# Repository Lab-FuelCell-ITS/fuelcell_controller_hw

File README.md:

# Fuel Cell Controller — Hardware

This repository contains the KiCad schematic and PCB hardware design for the Fuel Cell Controller developed by **Lab-FuelCell-ITS**. The project includes complete KiCad source files, symbol/footprint libraries, and backups used for designing, modifying, and fabricating the controller board.

<!-- 
 -->
<div style="display: flex; justify-content: center; gap: 10px;">

</div>

---

## Features

- Full KiCad project (schematics + PCB layout)
- Custom symbol and footprint libraries
- Backup snapshots for restoration
- Ready for Gerber and BOM generation
- Structured for collaboration and long-term maintenance

---

## Repository Contents

- `fuelcell.kicad_pro` — main KiCad project file  
- `fuelcell.kicad_sch` — schematic  
- `fuelcell.kicad_pcb` — PCB layout  
- `fuel_cell_lib.kicad_sym` — symbol library  
- `fuel_cell_foot.pretty/` — footprint library  
- `fuelcell-backups/` — automatic KiCad backups  
- KiCad metadata: `fp-lib-table`, `sym-lib-table`, `fp-info-cache`, etc.

---

## Notes for next update
- CAN label flipped
- added more space between DC-DC connector
- Nextion should supplied from 5v

--- 

## Requirements

- **KiCad (v9 or newer)**  
  Older versions may open the project but can cause compatibility issues.
  
---

## BOM
[BOM](https://docs.google.com/spreadsheets/d/1h5o9iBbPZtMF7gXZkPm5TLBS_tpg8lyO8AkKIXZHr1Q/edit?gid=0#gid=0)

list belanja
---

## How to Open the Project

1. Clone the repository:
   ```bash
   git clone https://github.com/Lab-FuelCell-ITS/fuelcell_controller_hw.git
   cd fuelcell_controller_hw

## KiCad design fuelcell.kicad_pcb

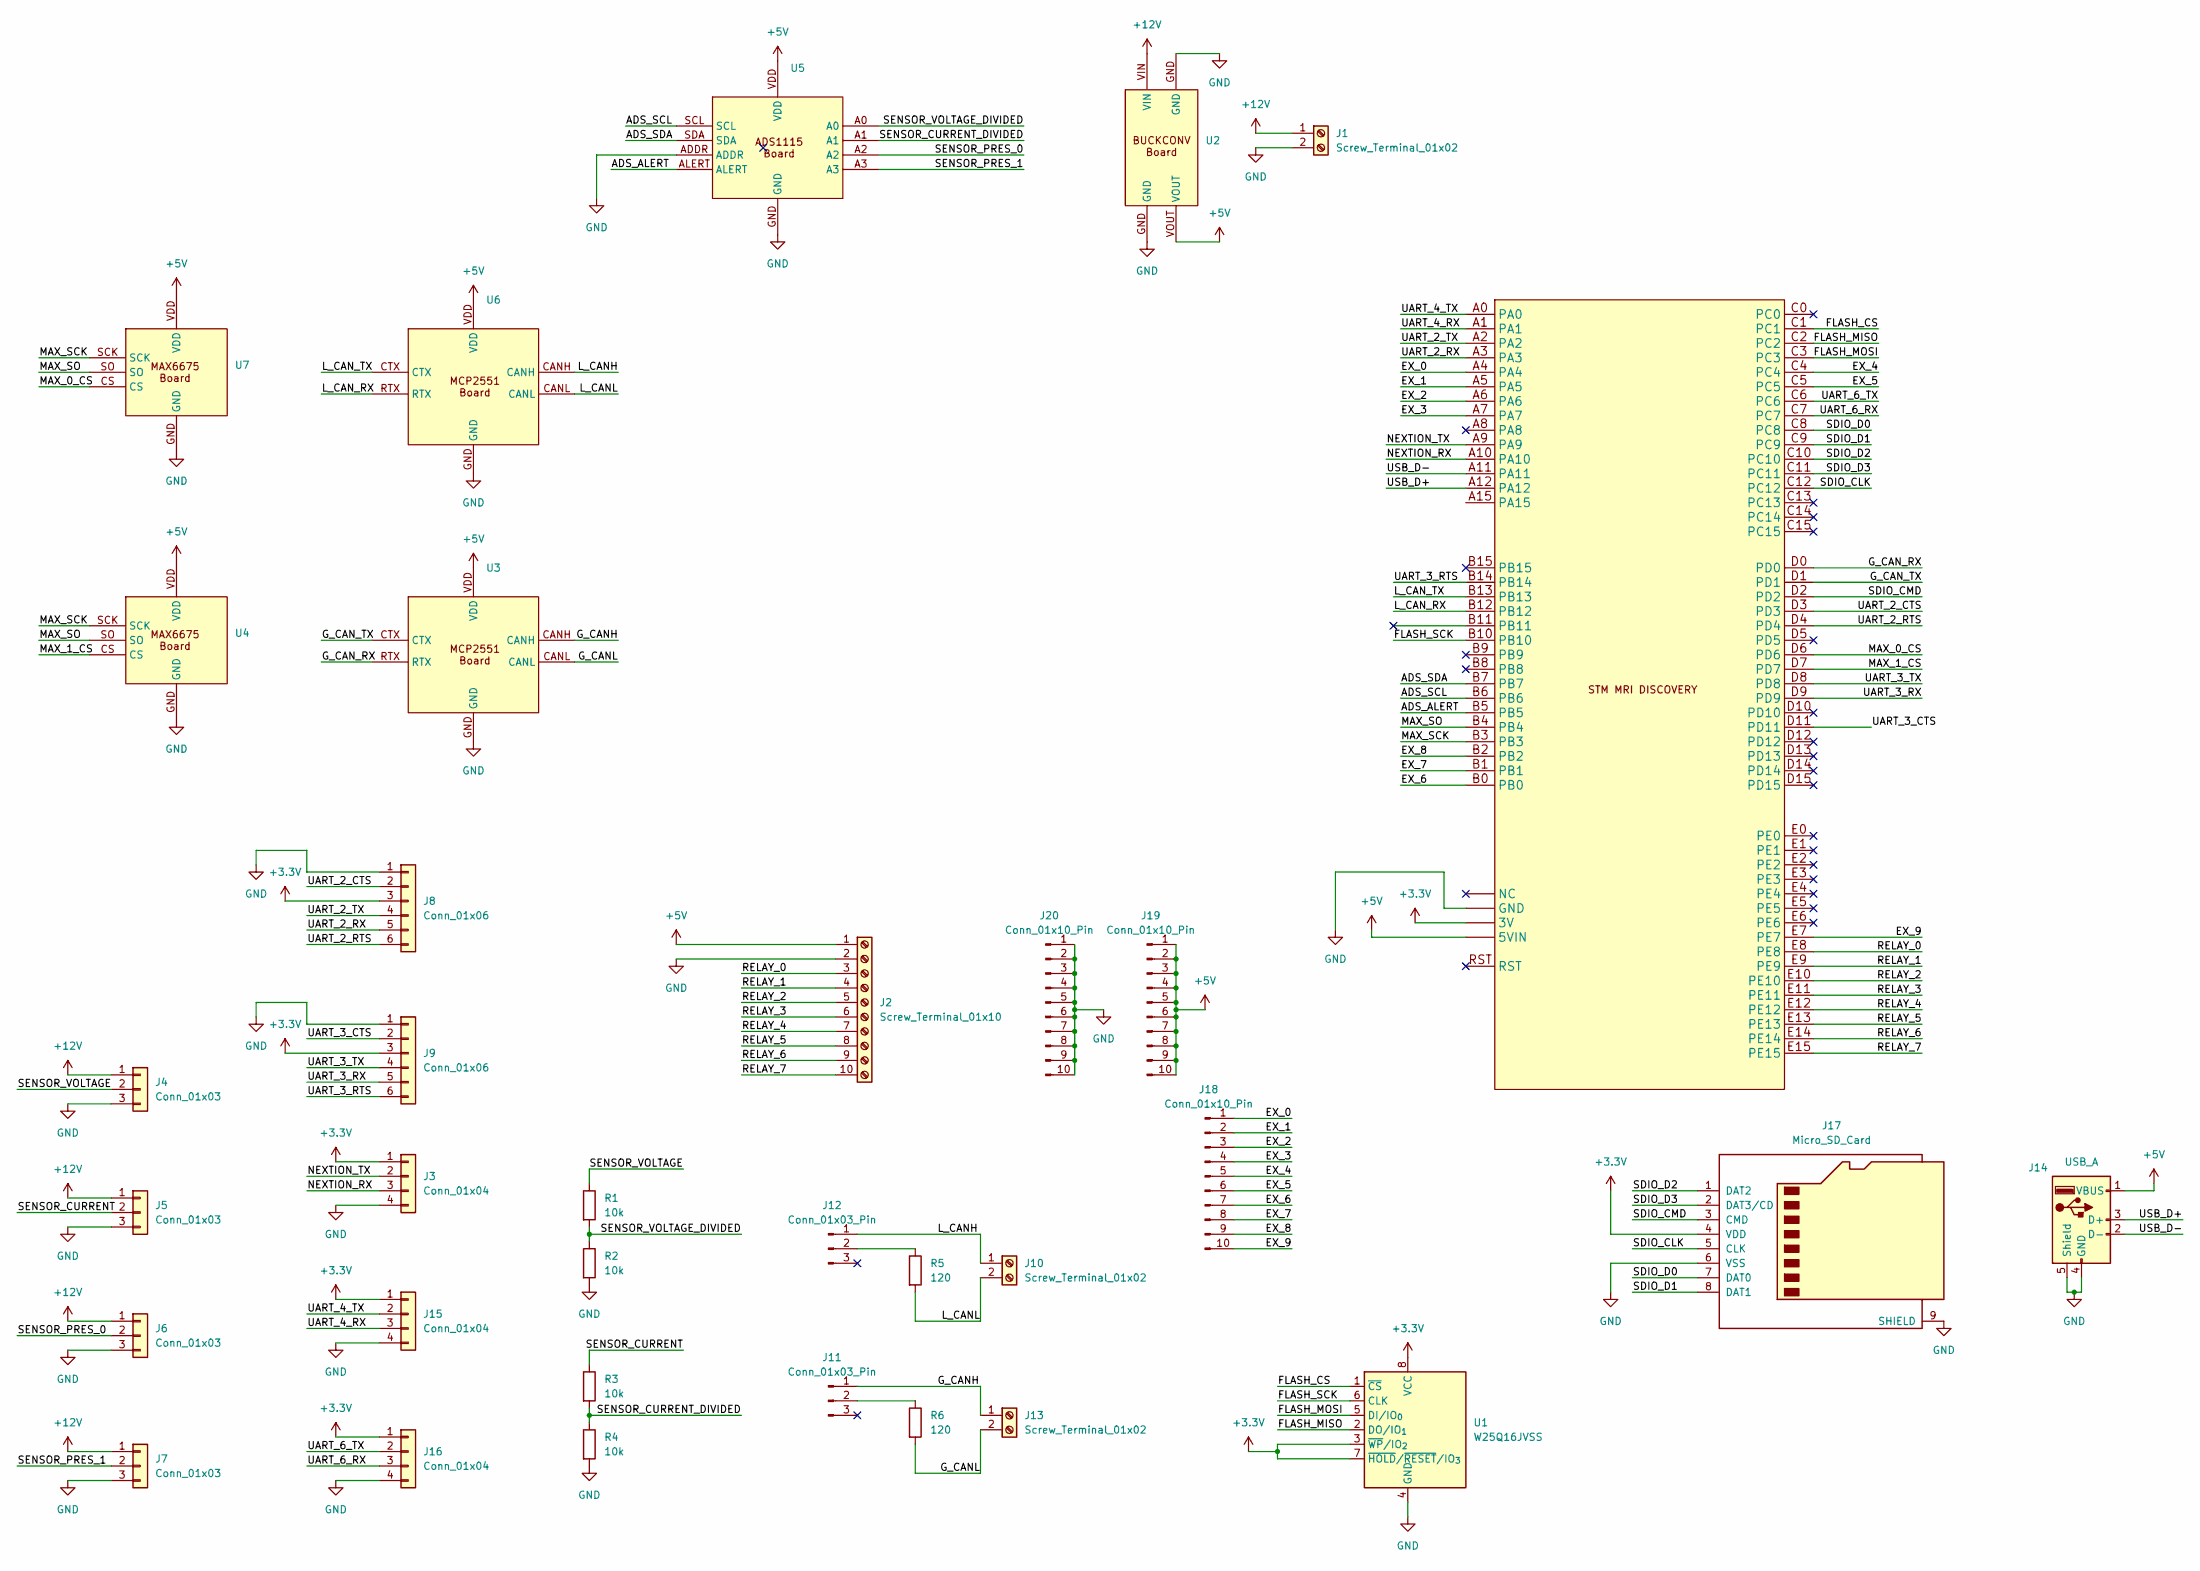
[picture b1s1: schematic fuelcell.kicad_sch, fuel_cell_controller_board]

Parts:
J1, J10, J13: Screw_Terminal_01x02; TerminalBlock_Phoenix_MKDS-1,5-2-5.08_1x02_P5.08mm_Horizont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
J2: Screw_Terminal_01x10; TerminalBlock_Phoenix_MKDS-3-10-5.08_1x10_P5.08mm_Horizontal
J3, J15, J16: Conn_01x04; PinHeader_1x04_P2.54mm_Vertical
J4, J5, J6, J7: Conn_01x03; PinHeader_1x03_P2.54mm_Vertical
J8, J9: Conn_01x06; PinHeader_1x06_P2.54mm_Vertical
J11, J12: Conn_01x03_Pin; PinHeader_1x03_P2.54mm_Vertical
J14: USB_A; USB_A_Molex_67643_Horizontal
J17: Micro_SD_Card; microSD_HC_Molex_47219-2001
J18, J19, J20: Conn_01x10_Pin; PinHeader_1x10_P2.54mm_Vertical
R1, R2, R3, R4: 10k; R_Axial_DIN0207_L6.3mm_D2.5mm_P10.16mm_Horizontal
R5, R6: 120; R_Axial_DIN0207_L6.3mm_D2.5mm_P10.16mm_Horizontal
U1: W25Q16JVSS; SOIC-8_5.3x5.3mm_P1.27mm
U2: Buck_Board
U3, U6: MCP2551_Board
U4, U7: MAX6675_Board
U5: ADS1115_Board
U8: STM32F4HEAD

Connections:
+3.3V: J3.1, J8.3, J9.3, J15.1, J16.1, J17.4 (VDD), U1.3 (~WP/IO_{2}), U1.7 (~HOLD/~RESET/IO_{3}), U1.8 (VCC), U8.3V1 (3V), U8.3V2 (3V), U8.3V3 (3V)
+5V: J2.1, J14.1 (VBUS), J19.1, J19.2, J19.3, J19.4, J19.5, J19.6, J19.7, J19.8, J19.9, J19.10, U2.VOUT, U3.VDD, U4.VDD, U5.VDD, U6.VDD, U7.VDD, U8.5V1 (5VIN), U8.5V2 (5VIN)
+12V: J1.1, J4.1, J5.1, J6.1, J7.1, U2.VIN
/ADS_ALERT: U5.ALERT, U8.B5
/ADS_SCL: U5.SCL, U8.B6
/ADS_SDA: U5.SDA, U8.B7
/EX_0: J18.1, U8.A4
/EX_1: J18.2, U8.A5
/EX_2: J18.3, U8.A6
/EX_3: J18.4, U8.A7
/EX_4: J18.5, U8.C4
/EX_5: J18.6, U8.C5
/EX_6: J18.7, U8.B0
/EX_7: J18.8, U8.B1
/EX_8: J18.9, U8.B2
/EX_9: J18.10, U8.E7
/FLASH_CS: U1.1 (~CS), U8.C1
/FLASH_MISO: U1.2 (DO/IO_{1}), U8.C2
/FLASH_MOSI: U1.5 (DI/IO_{0}), U8.C3
/FLASH_SCK: U1.6 (CLK), U8.B10
/G_CANH: J11.1, J13.1, U3.CANH
/G_CANL: J13.2, R6.2, U3.CANL
/G_CAN_RX: U3.RTX, U8.D0
/G_CAN_TX: U3.CTX, U8.D1
/L_CANH: J10.1, J12.1, U6.CANH
/L_CANL: J10.2, R5.2, U6.CANL
/L_CAN_RX: U6.RTX, U8.B12
/L_CAN_TX: U6.CTX, U8.B13
/MAX_0_CS: U7.CS, U8.D6
/MAX_1_CS: U4.CS, U8.D7
/MAX_SCK: U4.SCK, U7.SCK, U8.B3
/MAX_SO: U4.SO, U7.SO, U8.B4
/NEXTION_RX: J3.3, U8.A10
/NEXTION_TX: J3.2, U8.A9
/RELAY_0: J2.3, U8.E8
/RELAY_1: J2.4, U8.E9
/RELAY_2: J2.5, U8.E10
/RELAY_3: J2.6, U8.E11
/RELAY_4: J2.7, U8.E12
/RELAY_5: J2.8, U8.E13
/RELAY_6: J2.9, U8.E14
/RELAY_7: J2.10, U8.E15
/SDIO_CLK: J17.5 (CLK), U8.C12
/SDIO_CMD: J17.3 (CMD), U8.D2
/SDIO_D0: J17.7 (DAT0), U8.C8
/SDIO_D1: J17.8 (DAT1), U8.C9
/SDIO_D2: J17.1 (DAT2), U8.C10
/SDIO_D3: J17.2 (DAT3/CD), U8.C11
/SENSOR_CURRENT: J5.2, R3.1
/SENSOR_CURRENT_DIVIDED: R3.2, R4.1, U5.A1
/SENSOR_PRES_0: J6.2, U5.A2
/SENSOR_PRES_1: J7.2, U5.A3
/SENSOR_VOLTAGE: J4.2, R1.1
/SENSOR_VOLTAGE_DIVIDED: R1.2, R2.1, U5.A0
/UART_2_CTS: J8.2, U8.D3
/UART_2_RTS: J8.6, U8.D4
/UART_2_RX: J8.5, U8.A3
/UART_2_TX: J8.4, U8.A2
/UART_3_CTS: J9.2, U8.D11
/UART_3_RTS: J9.6, U8.B14
/UART_3_RX: J9.5, U8.D9
/UART_3_TX: J9.4, U8.D8
/UART_4_RX: J15.3, U8.A1
/UART_4_TX: J15.2, U8.A0
/UART_6_RX: J16.3, U8.C7
/UART_6_TX: J16.2, U8.C6
/USB_D+: J14.3 (D+), U8.A12
/USB_D-: J14.2 (D-), U8.A11
GND: J1.2, J2.2, J3.4, J4.3, J5.3, J6.3, J7.3, J8.1, J9.1, J14.4 (GND), J14.5 (Shield), J15.4, J16.4, J17.6 (VSS), J17.9 (SHIELD), J20.1, J20.2, J20.3, J20.4, J20.5, J20.6, J20.7, J20.8, J20.9, J20.10, R2.2, R4.2, U1.4 (GND), U2.GND, U3.GND, U4.GND, U5.ADDR, U5.GND, U6.GND, U7.GND, U8.GND1 (GND), U8.GND2 (GND), U8.GND3 (GND)
unnamed: J11.2, R6.1
unnamed: J12.2, R5.1

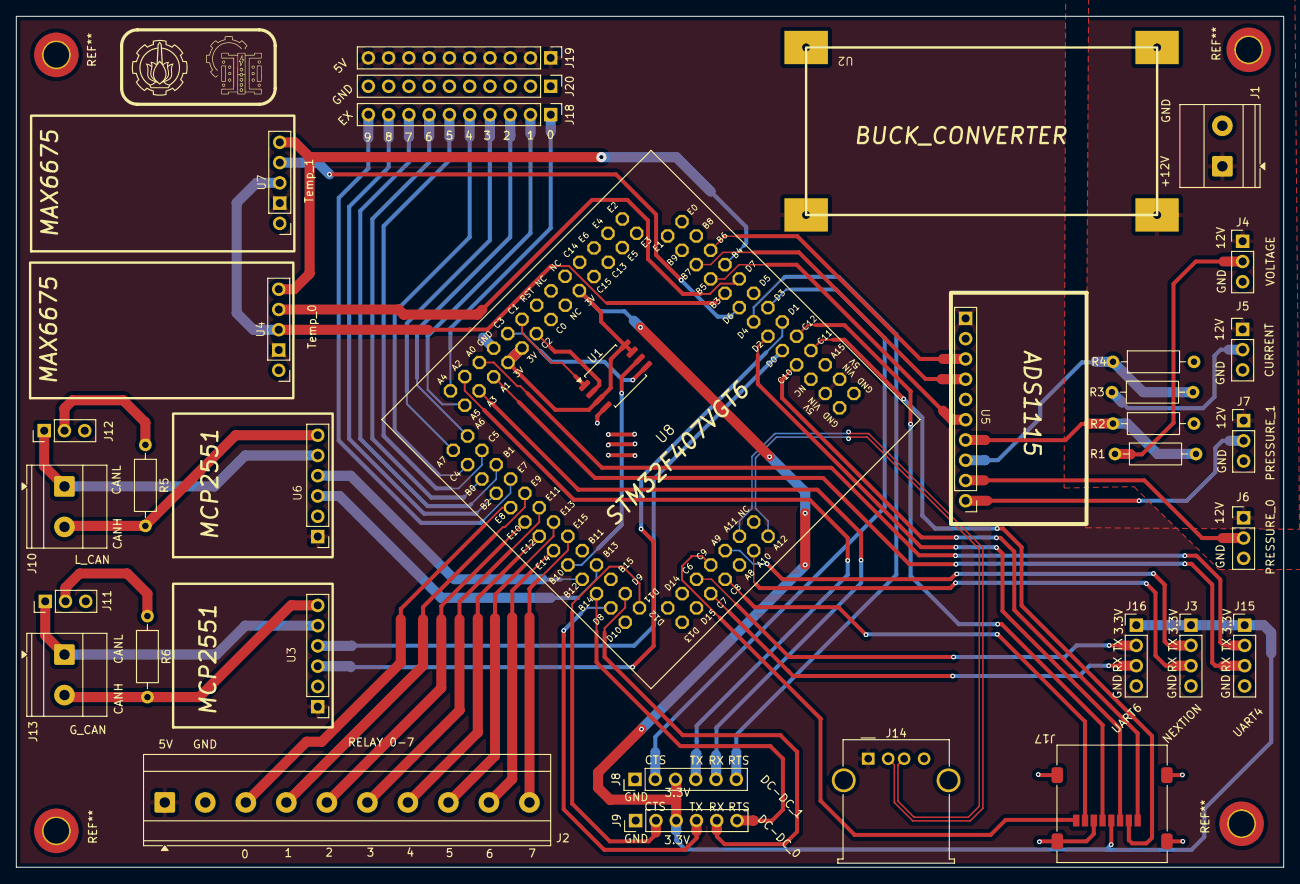
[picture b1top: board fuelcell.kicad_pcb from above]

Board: 2 copper layers, 158.9 x 106.7 mm, 34 parts (0 on the bottom side), 71 nets.

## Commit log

2025-11-19 added hardware version 1.0
2025-11-19 Change image alignment to flexbox in README.md
    Updated image display format in README.md for better layout.
